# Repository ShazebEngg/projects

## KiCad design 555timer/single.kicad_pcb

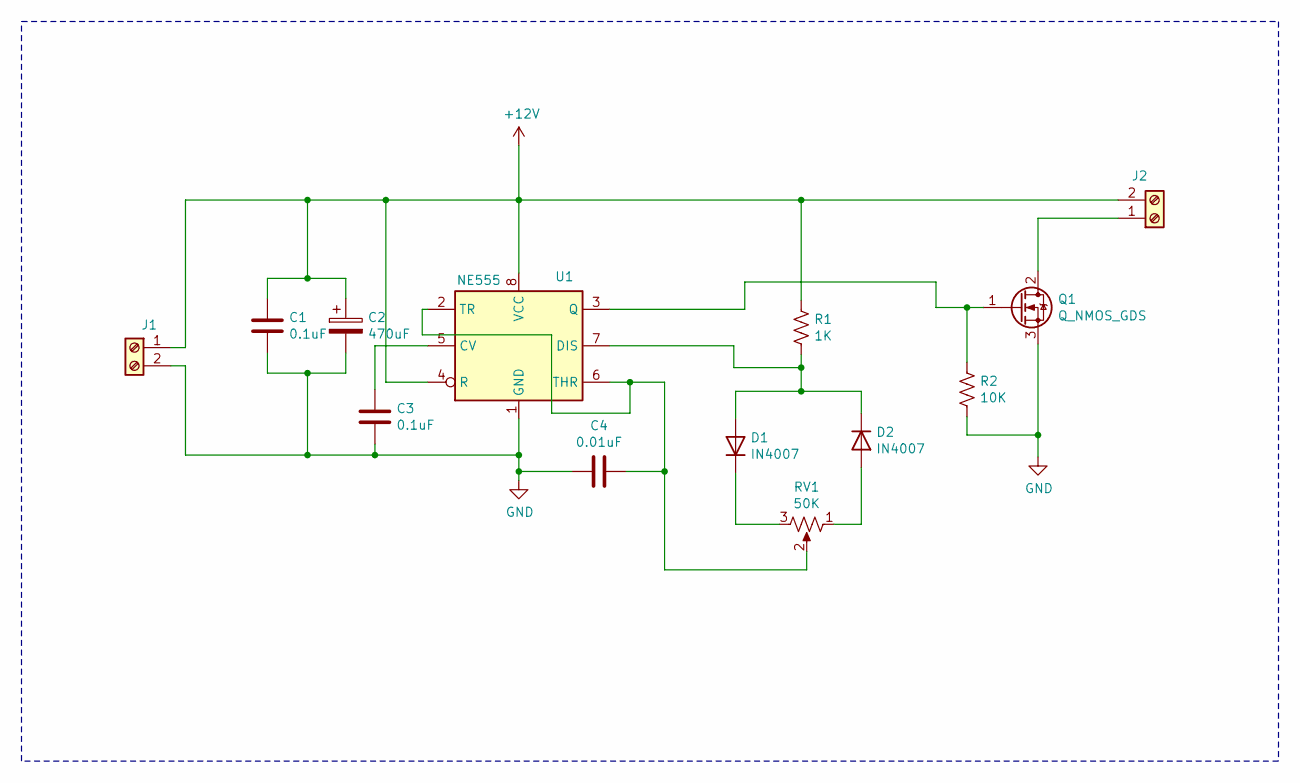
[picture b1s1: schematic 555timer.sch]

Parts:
C1, C3: 0.1uF; C_Disc_D3.8mm_W2.6mm_P2.50mm
C2: 470uF; CP_Radial_D6.3mm_P2.50mm
C4: 0.01uF; C_Disc_D3.8mm_W2.6mm_P2.50mm
D1, D2: IN4007; D_A-405_P7.62mm_Horizontal
J1, J2: Screw_Terminal_01x02; TerminalBlock_Phoenix_MKDS-1,5-2-5.08_1x02_P5.08mm_Horizont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
Q1: Q_NMOS_GDS; TO-220-3_Vertical
R1: 1K; R_Axial_DIN0207_L6.3mm_D2.5mm_P7.62mm_Horizontal
R2: 10K; R_Axial_DIN0207_L6.3mm_D2.5mm_P7.62mm_Horizontal
RV1: 50K; Potentiometer_Bourns_3386C_Horizontal
U1: NE555; DIP-8_W7.62mm_LongPads

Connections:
+12V: C1.1, C2.1, J1.1, J2.2, R1.1, U1.4 (R), U1.8 (VCC)
GND: C1.2, C2.2, C3.2, C4.2, J1.2, Q1.3 (S), R2.2, U1.1 (GND)
unnamed: C3.1, U1.5 (CV)
unnamed: C4.1, RV1.2, U1.2 (TR), U1.6 (THR)
unnamed: D1.1 (K), RV1.3
unnamed: D1.2 (A), D2.1 (K), R1.2, U1.7 (DIS)
unnamed: D2.2 (A), RV1.1
unnamed: J2.1, Q1.2 (D)
unnamed: Q1.1 (G), R2.1, U1.3 (Q)

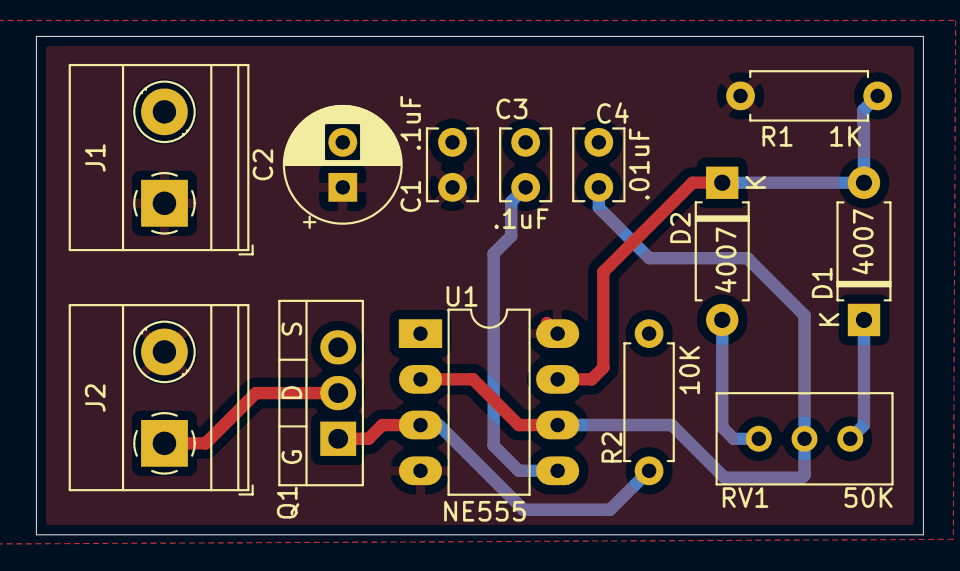
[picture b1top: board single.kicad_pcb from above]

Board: 2 copper layers, 49.3 x 27.7 mm, 13 parts (0 on the bottom side), 9 nets.

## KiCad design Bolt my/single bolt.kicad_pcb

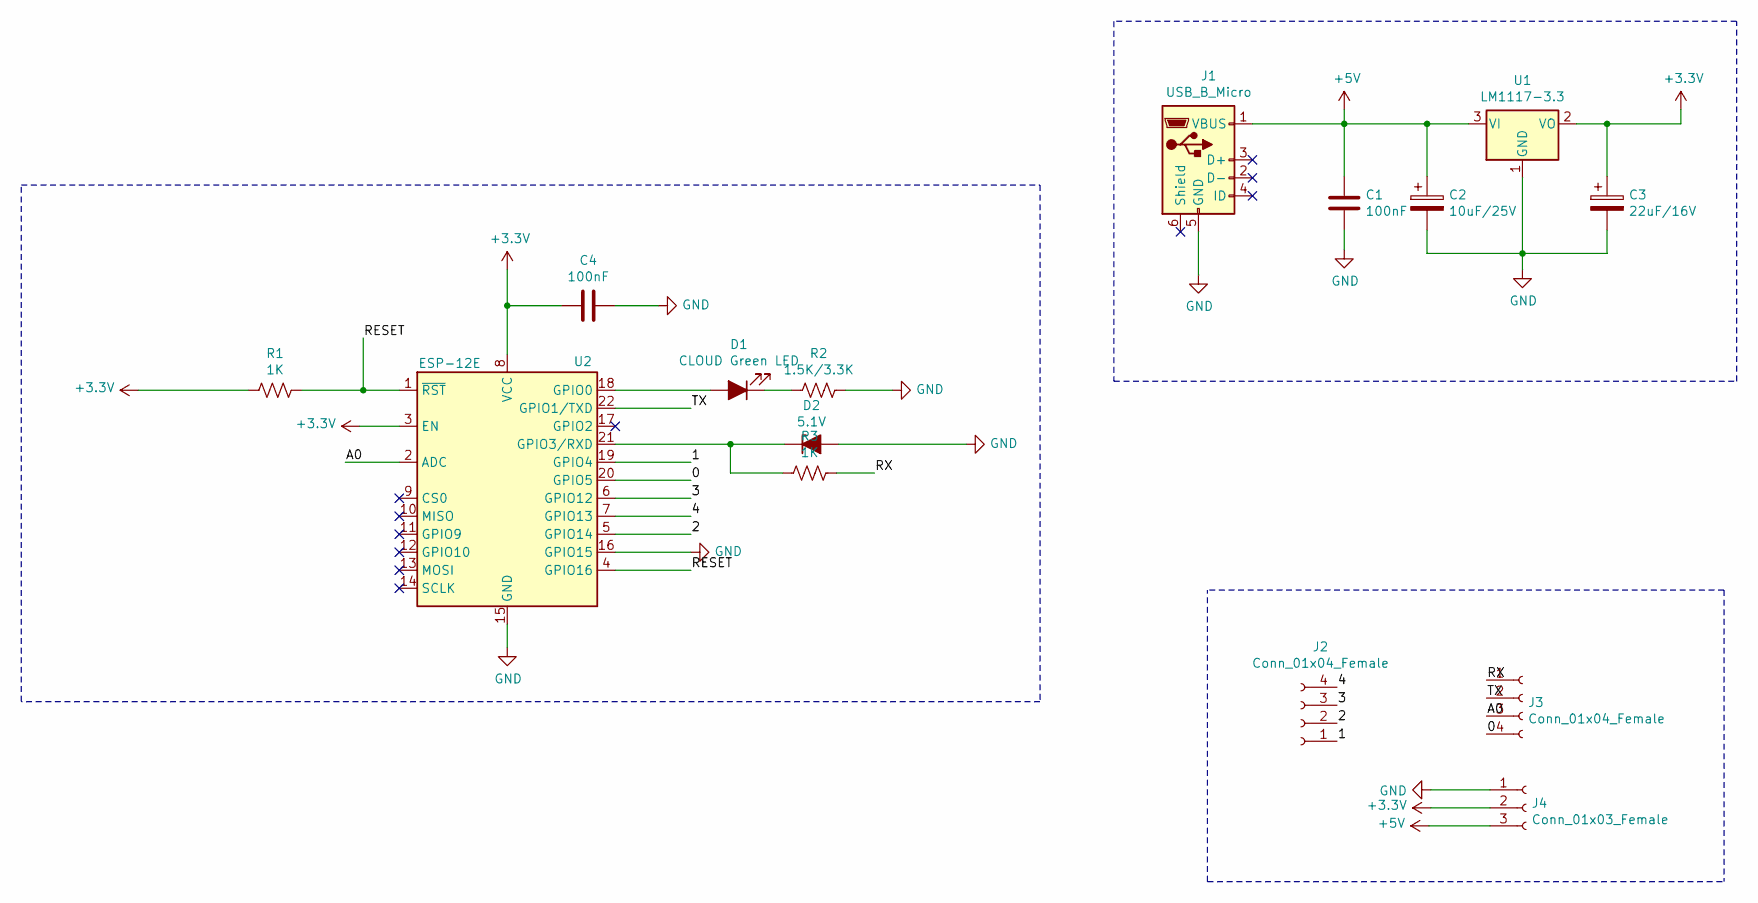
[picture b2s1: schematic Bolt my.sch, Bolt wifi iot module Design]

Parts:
C1, C4: 100nF; C_0805_2012Metric_Pad1.15x1.40mm_HandSolder
C2: 10uF/25V; C_Elec_3x5.4
C3: 22uF/16V; C_Elec_3x5.4
D1: CLOUD Green LED; LED_0805_2012Metric_Pad1.15x1.40mm_HandSolder
D2: 5.1V; D_MiniMELF_Handsoldering
J1: USB_B_Micro; USB_Micro-B_GCT_USB3076-30-A
J2, J3: Conn_01x04_Female; PinSocket_1x04_P2.54mm_Vertical
J4: Conn_01x03_Female; PinSocket_1x03_P2.54mm_Vertical
R1, R3: 1K; R_0805_2012Metric_Pad1.15x1.40mm_HandSolder
R2: 1.5K/3.3K; R_0805_2012Metric_Pad1.15x1.40mm_HandSolder
U1: LM1117-3.3; SOT-223
U2: ESP-12E

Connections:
+3V3: C3.1, C4.2, J4.2, R1.2, U1.2 (VO), U2.3 (EN), U2.8 (VCC)
+5V: C1.1, C2.1, J1.1 (VBUS), J4.3, U1.3 (VI)
/0: J3.4, U2.20 (GPIO5)
/1: J2.1, U2.19 (GPIO4)
/2: J2.2, U2.5 (GPIO14)
/3: J2.3, U2.6 (GPIO12)
/4: J2.4, U2.7 (GPIO13)
/A0: J3.3, U2.2 (ADC)
/RESET: R1.1, U2.1 (~RST), U2.4 (GPIO16)
/RX: J3.1, R3.1
/TX: J3.2, U2.22 (GPIO1/TXD)
GND: C1.2, C2.2, C3.2, C4.1, D2.2 (A), J1.5 (GND), J4.1, R2.1, U1.1 (GND), U2.15 (GND), U2.16 (GPIO15)
unnamed: D1.1 (K), R2.2
unnamed: D1.2 (A), U2.18 (GPIO0)
unnamed: D2.1 (K), R3.2, U2.21 (GPIO3/RXD)

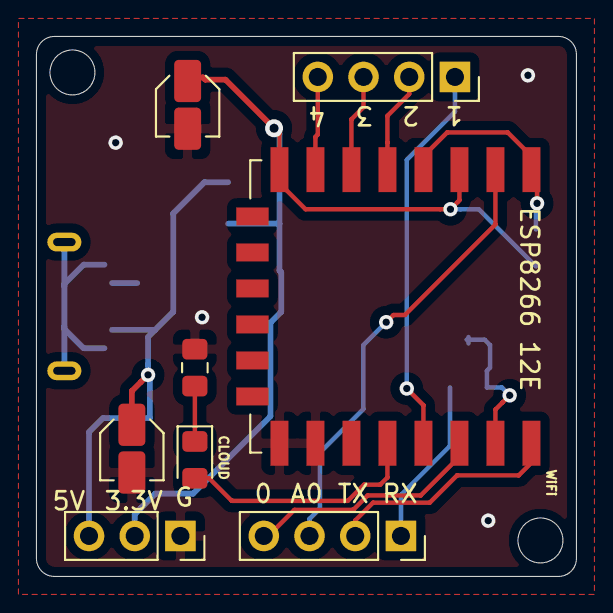
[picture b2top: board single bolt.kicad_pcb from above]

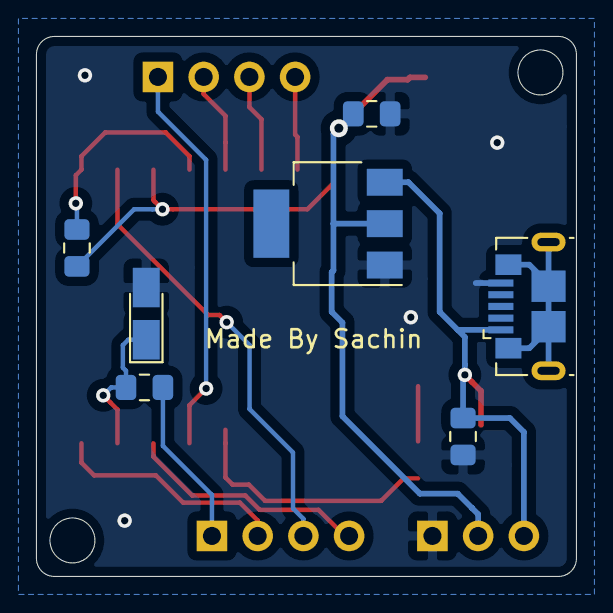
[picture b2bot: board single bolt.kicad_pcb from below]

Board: 2 copper layers, 30.0 x 30.0 mm, 15 parts (7 on the bottom side), 15 nets.

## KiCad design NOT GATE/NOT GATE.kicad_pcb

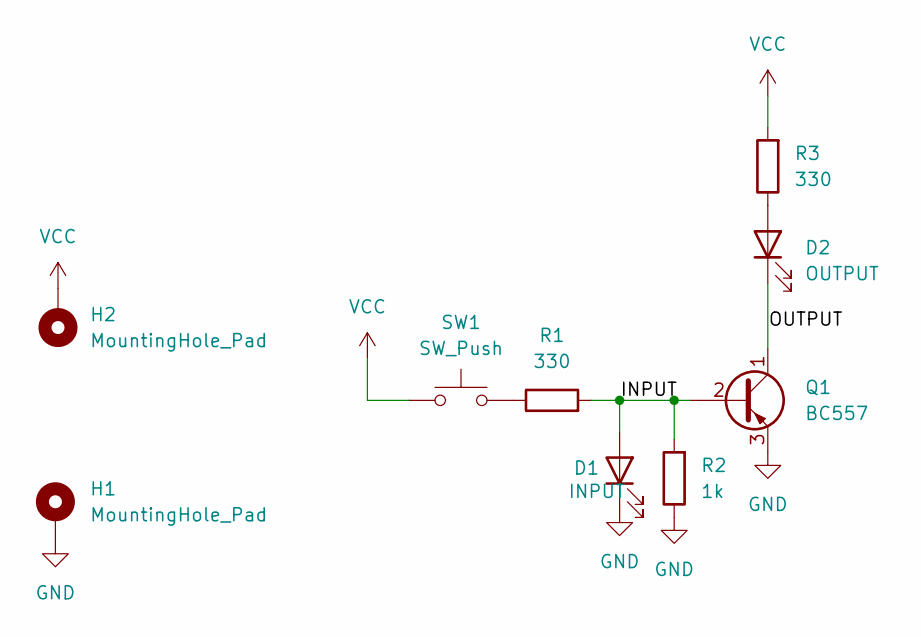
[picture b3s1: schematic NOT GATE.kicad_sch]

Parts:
D1: INPUT; LED_D3.0mm
D2: OUTPUT; LED_D3.0mm
H1, H2: MountingHole_Pad; MountingHole_2.2mm_M2_Pad_TopOnly
Q1: BC557; TO-92_Inline
R1, R3: 330; R_Axial_DIN0309_L9.0mm_D3.2mm_P12.70mm_Horizontal
R2: 1k; R_Axial_DIN0309_L9.0mm_D3.2mm_P12.70mm_Horizontal
SW1: SW_Push; SW_PUSH_6mm

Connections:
/INPUT: D1.2 (A), Q1.2 (B), R1.2, R2.2
/OUTPUT: D2.1 (K), Q1.1 (C)
GND: D1.1 (K), H1.1, Q1.3 (E), R2.1
unnamed: D2.2 (A), R3.1
unnamed: R1.1, SW1.2
VCC: H2.1, R3.2, SW1.1

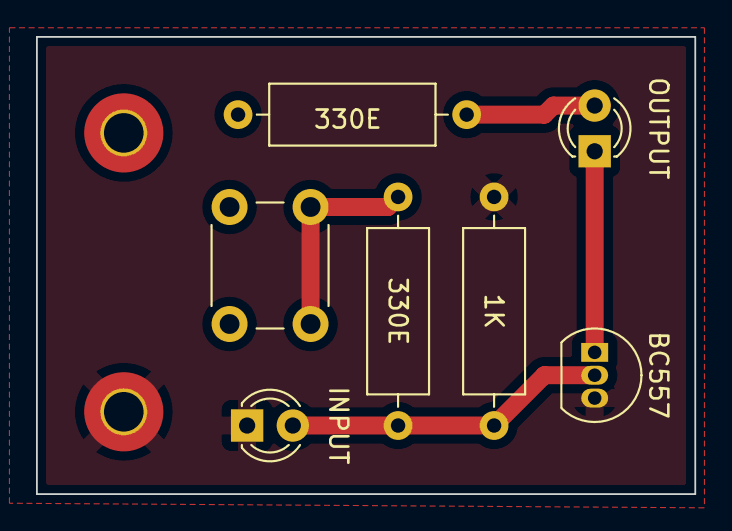
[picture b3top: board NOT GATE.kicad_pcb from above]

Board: 2 copper layers, 36.6 x 25.4 mm, 9 parts (0 on the bottom side), 6 nets.

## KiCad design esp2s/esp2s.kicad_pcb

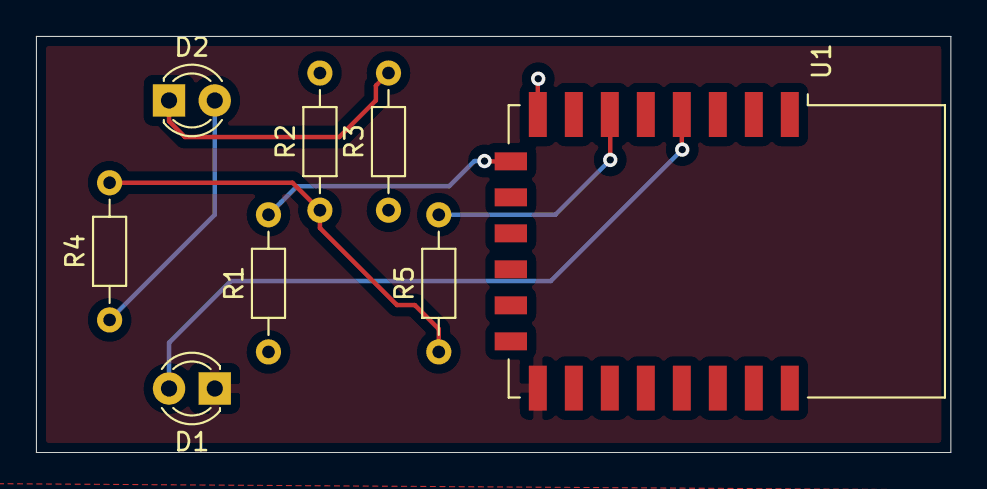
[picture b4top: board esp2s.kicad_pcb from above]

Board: 2 copper layers, 50.8 x 23.1 mm, 8 parts (0 on the bottom side), 8 nets.

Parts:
D1, D2: LED; LED_D3.0mm_FlatTop
R1, R2, R3, R4, R5: R; R_Axial_DIN0204_L3.6mm_D1.6mm_P7.62mm_Horizontal
U1: ESP-12F; ESP-12E

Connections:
+5V: R1.1, R2.2, R3.1, U1.8
GND: D1.1, U1.15
unnamed: D1.2, U1.4
unnamed: D2.1, R3.2
unnamed: D2.2, R4.1
unnamed: R1.2, U1.9
unnamed: R2.1, R4.2, R5.1
unnamed: R5.2, U1.6

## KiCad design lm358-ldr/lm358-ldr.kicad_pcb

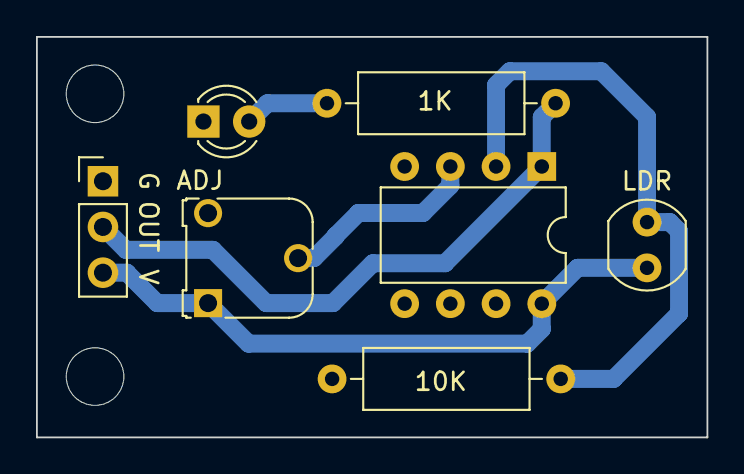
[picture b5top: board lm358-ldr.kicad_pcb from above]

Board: 2 copper layers, 37.2 x 22.2 mm, 7 parts (0 on the bottom side), 6 nets.

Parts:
1K, 10K: R; R_Axial_DIN0309_L9.0mm_D3.2mm_P12.70mm_Horizontal
ADJ: R_Potentiometer; Potentiometer_Runtron_RM-065_Vertical
D1: LED; LED_D3.0mm
J1: Conn_01x03_Male; PinHeader_1x03_P2.54mm_Vertical
LDR: R_Photo; R_LDR_4.9x4.2mm_P2.54mm_Vertical
U1: LM358; DIP-8_W7.62mm

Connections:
GND: 10K.2, ADJ.3, D1.1 (K), J1.1, U1.4 (V-)
unnamed: 1K.2, D1.2 (A)
unnamed: 10K.1, LDR.2, U1.2 (-)
unnamed: ADJ.2, U1.3 (+)
O/P: 1K.1, J1.2, U1.1
VCC: ADJ.1, J1.3, LDR.1, U1.8 (V+)

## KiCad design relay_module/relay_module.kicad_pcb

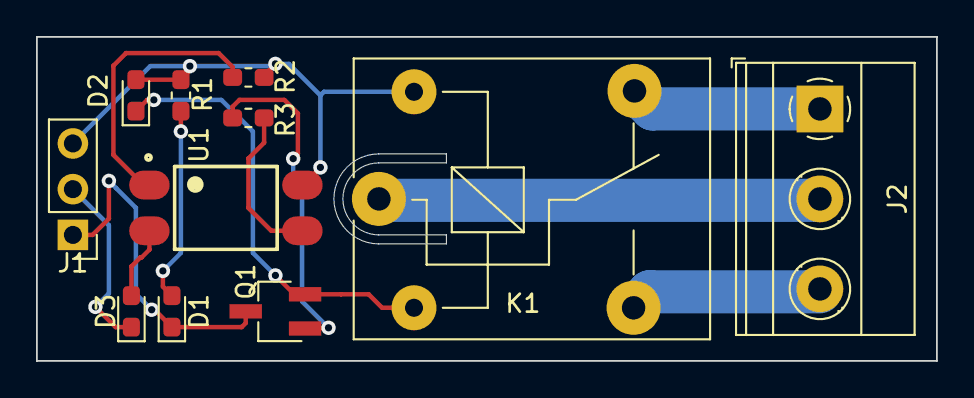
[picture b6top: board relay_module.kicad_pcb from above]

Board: 2 copper layers, 50.0 x 18.0 mm, 11 parts (0 on the bottom side), 12 nets.

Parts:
D1: Power LED; LED_0603_1608Metric_Pad1.05x0.95mm_HandSolder
D2: Freewheeling Diode; D_0603_1608Metric_Pad1.05x0.95mm_HandSolder
D3: Signal LED; LED_0603_1608Metric_Pad1.05x0.95mm_HandSolder
J1: Conn_01x03; PinHeader_1x03_P2.54mm_Vertical
J2: Screw_Terminal_01x03; TerminalBlock_Phoenix_MKDS-1,5-3_1x03_P5.00mm_Horizontal
K1: SANYOU_SRD_Form_C; Relay_SPDT_SANYOU_SRD_Series_Form_C
Q1: SWITCHING TRANSISTOR; SC-59_Handsoldering
R1, R2: 1K; R_0603_1608Metric_Pad1.05x0.95mm_HandSolder
R3: 560 ohms; R_0603_1608Metric_Pad1.05x0.95mm_HandSolder
U1: PC817X2NIP0F; SOT254P975X400-4N

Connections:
GND: D1.1, J1.1, Q1.3
IN: D3.1, J1.2
unnamed: D1.2, R1.1
unnamed: D2.1, K1.2, Q1.2
unnamed: D3.2, U1.2
unnamed: J2.1, K1.4
unnamed: J2.2, K1.1
unnamed: J2.3, K1.3
unnamed: Q1.1, R3.1
unnamed: R2.1, U1.1
unnamed: R3.2, U1.3
VCC: D2.2, J1.3, K1.5, R1.2, R2.2, U1.4
